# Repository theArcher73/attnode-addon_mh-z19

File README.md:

# CO<sub>2</sub>-Sensor-Attnode mit MH-Z19
A small functional AddOn CO<sub>2</sub>-Sensor to use with a [attno.de v3](https://attno.de) and MH-Z19-CO<sub>2</sub>-Sensor

 pictures from [@seiichiro0185](https://twitter.com/seiichiro0185?s=20) | &nbsp;
 ---------------------------------------------------------------------- | --------
  | &nbsp;
  | 

You can find more information and the latest firmware at [attno.de v3](https://attno.de). [@seiichiro0185](https://twitter.com/seiichiro0185?s=20) is continuously developing the software, which is why it is only linked here.

This pcb allows the extension of the [attno.de v3](https://attno.de) with the possibility to be operated with 5V-15V operating voltage as well as CO<sub>2</sub> measurement by means of MH-Z19.

The measured values of the CO<sub>2</sub> sensor as well as the connection via LORAWAN<sup>(TM)</sup> can be visualized directly at the device by the integrated RGB-LED's, parallel to the transmission to a LoRa-Network-Server (LNS).

The use of the MH-Z19C is strongly recommended. However, this sensor drifts over time so regular calibration is required.
The sensor can be purchased over the Silk Road or directly from German dealers.

Special thanks to [@seiichiro0185](https://twitter.com/seiichiro0185?s=20), [@TwentySixer](https://twitter.com/Twenty_Sixer?s=20) and [@nottheedge](https://twitter.com/nottheedge?s=20) for their support.

front view | rear view
---------- | ---------
 |  

In the folder 3d-files are stl-Files for a tiny housing from [@seiichiro](https://twitter.com/seiichiro0185).

 front-part MH-Z19C | rear-part CO<sub>2</sub>-Sensor Micro-USB | rear-part CO<sub>2</sub>-Sensor USB-C
 ------------------ | ----------------------------------------- | -------------------------------------
 |  |  
&nbsp; | [passende Breakout-Boards Micro-USB](https://www.amazon.de/dp/B07RDHNL9H/ref=cm_sw_r_oth_apip_Hl8EULSynzB3m) | [passende Breakout-Boards USB-C](https://www.amazon.de/dp/B01787RJW4/ref=cm_sw_r_oth_apip_VpbGjvT7G7Qvm)

The rear parts of the enclosures for Micro-USB or USB-C are planned for the use of ready-made breakout boards with USB-C or micro USB. The button for ad-hoc measurements or calibration can be glued into the housing.

LORAWAN is a registered trademark of [Semtech](https://www.semtech.com/)

## Disclaimer

The documentation of the CO<sub>2</sub>-Sensor-Attnode mit MH-Z19 is distributed in the hope that it will be useful, but WITHOUT ANY WARRANTY; without even the implied warranty of MERCHANTABILITY or FITNESS FOR A PARTICULAR PURPOSE.

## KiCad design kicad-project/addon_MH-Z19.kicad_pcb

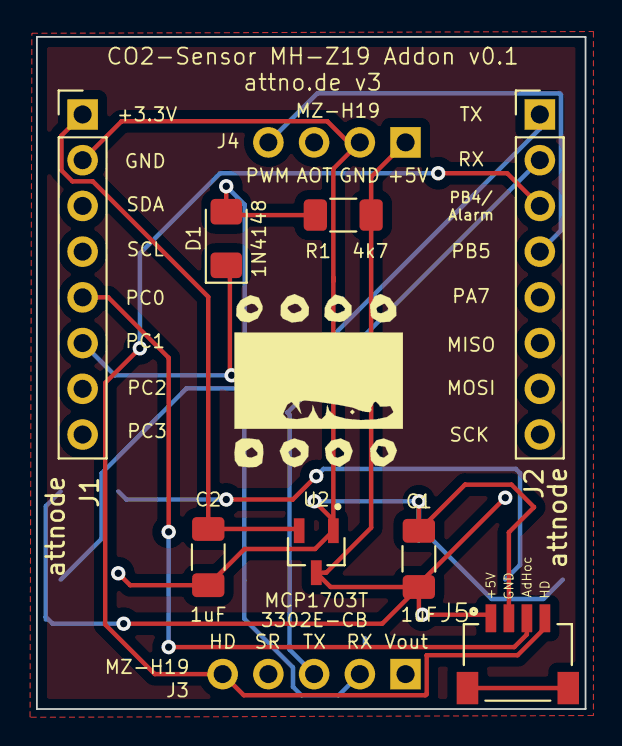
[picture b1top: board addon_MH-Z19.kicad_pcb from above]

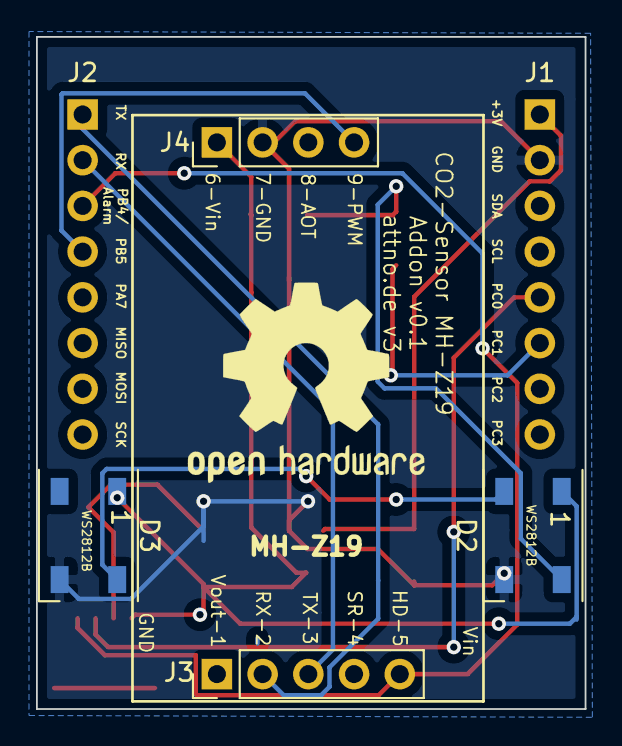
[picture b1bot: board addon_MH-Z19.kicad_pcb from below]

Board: 2 copper layers, 30.5 x 37.3 mm, 12 parts (4 on the bottom side), 12 nets.

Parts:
C1, C2: 1uF; C_1206_3216Metric_Pad1.33x1.80mm_HandSolder
D1: 1N4148; D_1206_3216Metric_Pad1.42x1.75mm_HandSolder
D2, D3: WS2812B; LED_WS2812B_PLCC4_5.0x5.0mm_P3.2mm
J1, J2: attnode; PinHeader_1x08_P2.54mm_Vertical
J3: MZ-H19; PinHeader_1x05_P2.54mm_Vertical
J4: MZ-H19; PinHeader_1x04_P2.54mm_Vertical
J5: SM04B-SRSS-TBT(LF)(SN); JST_SM04B-SRSS-TB(LF)(SN)
R1: 4k7; R_1206_3216Metric_Pad1.30x1.75mm_HandSolder
U2: MCP1703T; SOT95P255X145-3N

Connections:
+3V3: C2.1, J1.1, U2.2
+5V: C1.1, D2.1, D3.1, J4.1, J5.1, R1.1, U2.3
AdHoc: J1.5, J5.3
GND: C1.2, C2.2, D2.3, D3.3, J1.2, J4.2, J5.2, U2.1
HD: J2.3, J3.5, J5.4
unnamed: D1.2, D2.4, R1.2
unnamed: D2.2, D3.4
unnamed: J5.S1, J5.S2
PC1: D1.1, J1.6
PWM: J2.4, J4.4
RX: J2.2, J3.3
TX: J2.1, J3.2

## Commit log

2021-02-07 initial build
2021-02-07 pictures update
2021-02-07 bugfix
2021-02-07 added BOM
2021-02-07 beautyvier
2021-02-08 cleanup
2021-03-22 3d-files
2021-03-27 update foldername to lcase
2021-03-27 added pictures 3d-parts
2021-03-28 add pictures
2021-05-30 add disclaimer
